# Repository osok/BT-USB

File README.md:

#Description
I needed a device to be plugged into a USB port only when I wanted it to be, but I could not gain access to it or the USB port physically, I could only gain general proximity to it.

#Board Manufacturing
OSHPark, https://oshpark.com/, can be used to fabricate the board.  Simply upload the "BT USB All SMD.brd" and select how many you would like to have built.  OSHPak takes about 2 to 3 weeks to fabricate the board.  You will have to purchase 3 at a time.  When I last ordered the board it was $9.95 for 3.

A Stencil to mask solder paste can be create by uploading the "BT USB All SMD.brd" to OSHStencils, https://www.oshstencils.com/.

#Components
* RF22301, these cost about $20
* USB In
* USB Out
* EE2-3NUX I purchased mine from eBay for about $0.50 each.
* AMS1117 voltage regulator, cost about $1
* Pin headers for UART I had some laying around

As for the smd components I picked up some sample books of capacitors, transistors, resistors, diodes and the such with a verity of components from eBay.  So for me these pieces were less than a penny each.

# Note
Once you solder the RF22301 on to a board its there.  I have not been able to remove one from an old board.  

#Operation
I used nRF Connect, that I downloaded from the Google Play to connect and trigger the switch.

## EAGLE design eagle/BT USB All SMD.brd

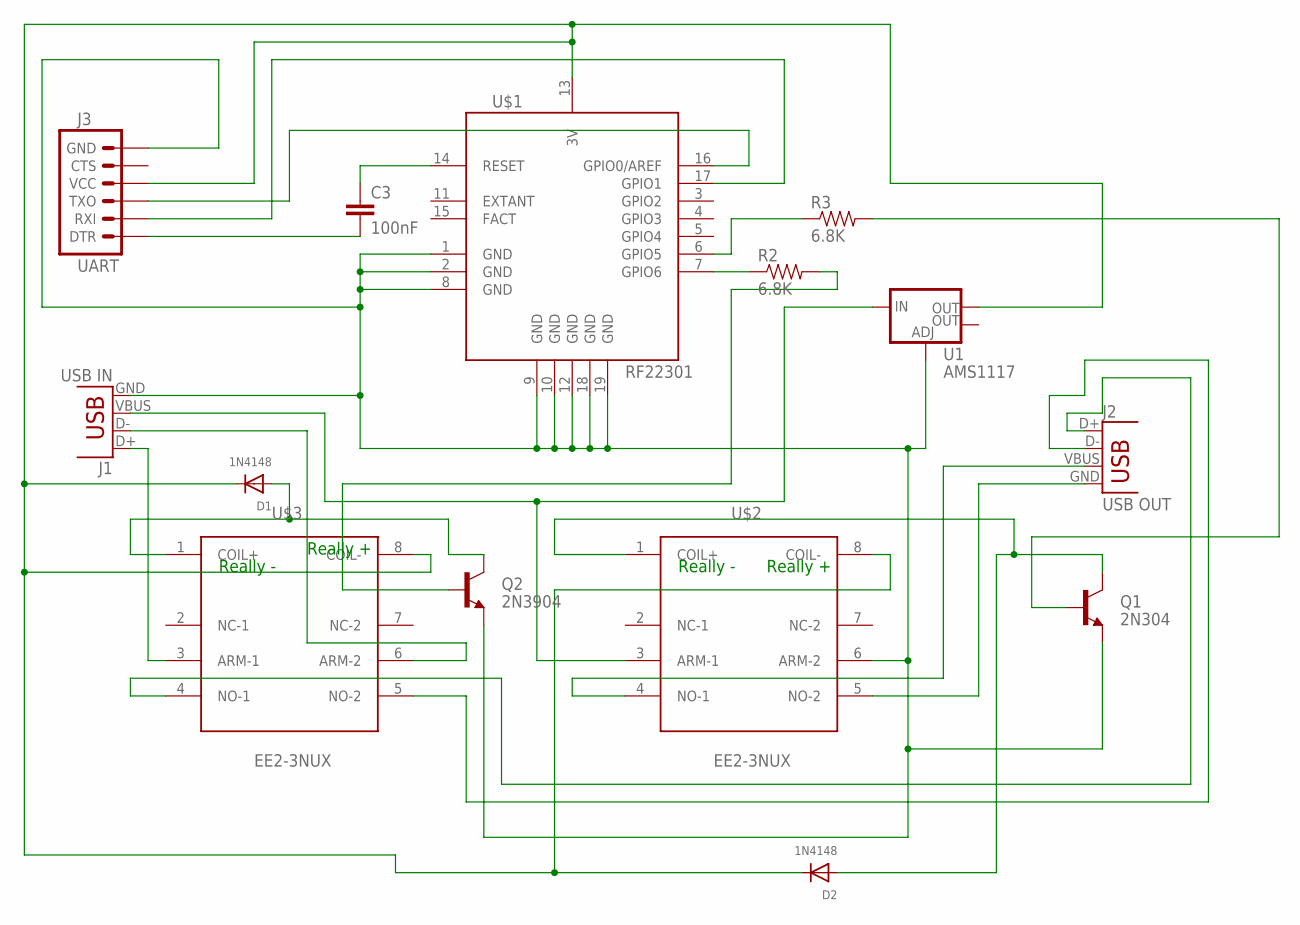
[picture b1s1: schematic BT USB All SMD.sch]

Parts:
C3: 100nF; 0805
D1, D2: 1N4148; SOD-123
J1: USB IN; USB-A-H
J2: USB OUT; USB-A-S
J3: UART; 1X06
Q1: 2N304; SOT23-3
Q2: 2N3904; SOT23-3
R2, R3: 6.8K; 0805
U1: AMS1117; SOT223
U$1: RF22301; RFD22301
U$2, U$3: RELAY-EE2-3NUX

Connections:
D_HIGH: J1.D+, U$3.3 (ARM-1)
D_HIGH_OUT: J2.D+, U$3.4 (NO-1)
D_LOW: J1.D-, U$3.6 (ARM-2)
D_LOW_OUT: J2.D-, U$3.5 (NO-2)
GND: J1.GND, J3.6 (GND), Q1.2 (E), Q2.2 (E), U1.1 (ADJ), U$1.1 (GND), U$1.2 (GND), U$1.8 (GND), U$1.9 (GND), U$1.10 (GND), U$1.12 (GND), U$1.18 (GND), U$1.19 (GND), U$2.6 (ARM-2)
GND_OUT: J2.GND, U$2.5 (NO-2)
unnamed: D1.A, Q2.3 (C), U$3.1 (COIL+)
unnamed: D2.A, Q1.3 (C), U$2.1 (COIL+)
unnamed: C3.1, U$1.14 (RESET)
unnamed: C3.2, J3.1 (DTR)
unnamed: J3.3 (TXO), U$1.16 (GPIO0/AREF)
unnamed: J3.2 (RXI), U$1.17 (GPIO1)
unnamed: Q2.1 (B), R2.2
unnamed: R2.1, U$1.7 (GPIO6)
unnamed: R3.1, U$1.6 (GPIO5)
unnamed: Q1.1 (B), R3.2
V3_3: D1.C, D2.C, J3.4 (VCC), U1.2 (OUT), U$1.13 (3V), U$2.8 (COIL-), U$3.8 (COIL-)
V5_0: J1.VBUS, U1.3 (IN), U$2.3 (ARM-1)
V5_0_OUT: J2.VBUS, U$2.4 (NO-1)

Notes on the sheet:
Really +
Really -

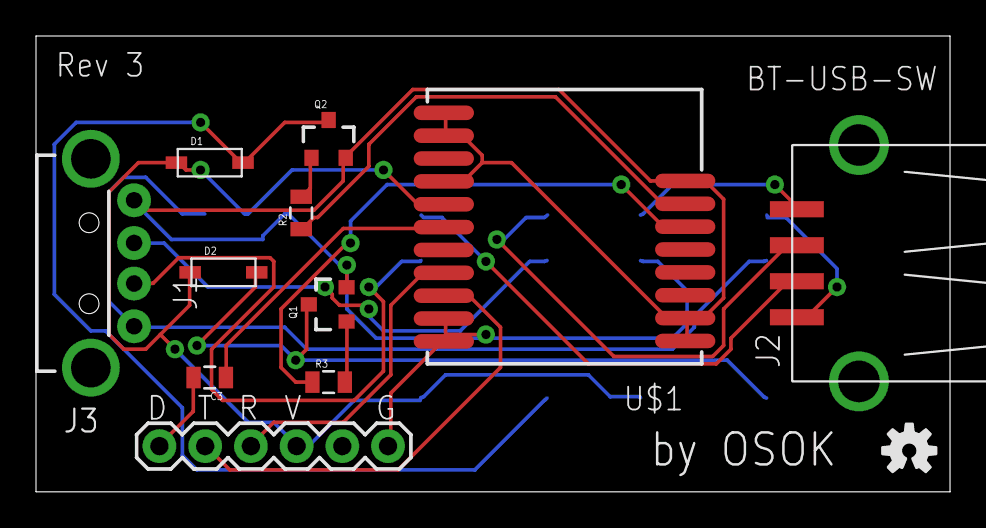
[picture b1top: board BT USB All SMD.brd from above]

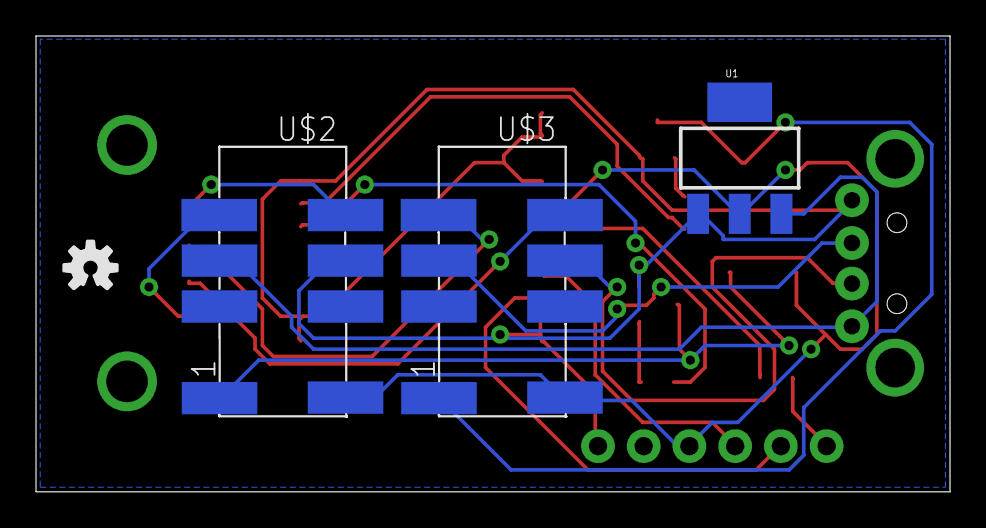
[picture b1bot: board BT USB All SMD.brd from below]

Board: 2 copper layers, 50.8 x 25.3 mm, 16 parts (4 on the bottom side), 19 nets.

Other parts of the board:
U$4, U$5: OSHW-LOGO-S

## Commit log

2017-01-19 :lollipop: Added .gitattributes & .gitignore files
2017-01-19 initial checkin

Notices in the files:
parts and their libraries:
SparkFun-Capacitors: Licensing: Creative Commons ShareAlike 4.0 International - https://creativecommons.org/licenses/by-sa/4.0
